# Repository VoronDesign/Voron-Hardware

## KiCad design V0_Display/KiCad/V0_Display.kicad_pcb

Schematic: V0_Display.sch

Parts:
C1, C2: 4.7uF; C_0805_2012Metric; LCSC C1779
C3, C4: 0.1uF; C_0805_2012Metric; LCSC C49678
D1: WS2812B; LED_WS2812B_PLCC4_5.0x5.0mm_P3.2mm
GPIO1: Conn_01x03; PinHeader_1x03_P2.54mm_Vertical
H1, H2, H3, H4: MountingHole; MountingHole_3.2mm_M3
J1: USB_B_Micro; MolexVertical&Horizontal_MicroB
J2: I2C Header 1; 1pt3in_OLED
J3: Conn_01x03; PinHeader_1x03_P2.54mm_Vertical
J4, J8: Conn_01x02; PinHeader_1x02_P2.54mm_Vertical
J5: SWD Header; PinHeader_2x05_P1.27mm_Vertical_SMD
J7: USB_Header; PinHeader_1x04_P2.54mm_Vertical
JP1: Pin2; SolderJumper-3_P1.3mm_Bridged12_Pad1.0x1.5mm
JP2: Pin1; SolderJumper-3_P1.3mm_Bridged12_Pad1.0x1.5mm
R1, R2, R3: 10K; R_0805_2012Metric; LCSC C17414
SW5, SW6: SW_SPST; SW_PUSH_6mm
SW7: Rotary_Encoder_Switch; EN11_Encoder
U1: AP2127K-3.3; SOT-23-5; LCSC C156285
U2: STM32F042F6Px; TSSOP-20_4.4x6.5mm_P0.65mm; LCSC C81000
U3: 74LVC1G17; SOT-753; LCSC C6076

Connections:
+3V3: C2.1, C3.2, C4.1, J4.1, J5.1, JP1.1, JP2.3, R1.1, R3.1, U1.5 (VOUT), U2.5, U2.16
BOOT0: J4.2, R2.1, U2.1
D+: J1.3, J7.3, U2.18
D-: J1.2, J7.2, U2.17
Encoder_A: SW7.A, U2.9
Encoder_B: SW7.B, U2.10
Encoder_Switch: SW7.S1, U2.7
GND: C1.2, C2.2, C3.1, C4.2, D1.3, J1.4, J1.5, J1.6, J5.3, J5.5, J7.4, J8.2, JP1.3, JP2.1, R2.2, SW5.2 (B), SW6.1, SW7.C, SW7.S2, U1.2 (GND), U2.15, U3.3
GPIO1: GPIO1.1, U2.12
GPIO2: GPIO1.2, U2.13
GPIO3: GPIO1.3, U2.14
Kill_Switch: SW6.2, U2.11
NeoPixel: U2.6, U3.2
unnamed: D1.2, J8.1
unnamed: D1.4, U3.4
Pin1: J2.1, JP2.2
Pin2: J2.2, JP1.2
SCL: J2.3, U2.3
SDA: J2.4, U2.2
SWDCLK: J3.2, J5.4, R3.2, U2.20
SWDIO: J3.1, J5.2, U2.19
VBUS: C1.1, D1.1, J1.1, J7.1, U1.1 (VIN), U1.3 (EN), U3.5
~Reset: J3.3, J5.10, R1.2, SW5.1 (A), U2.4

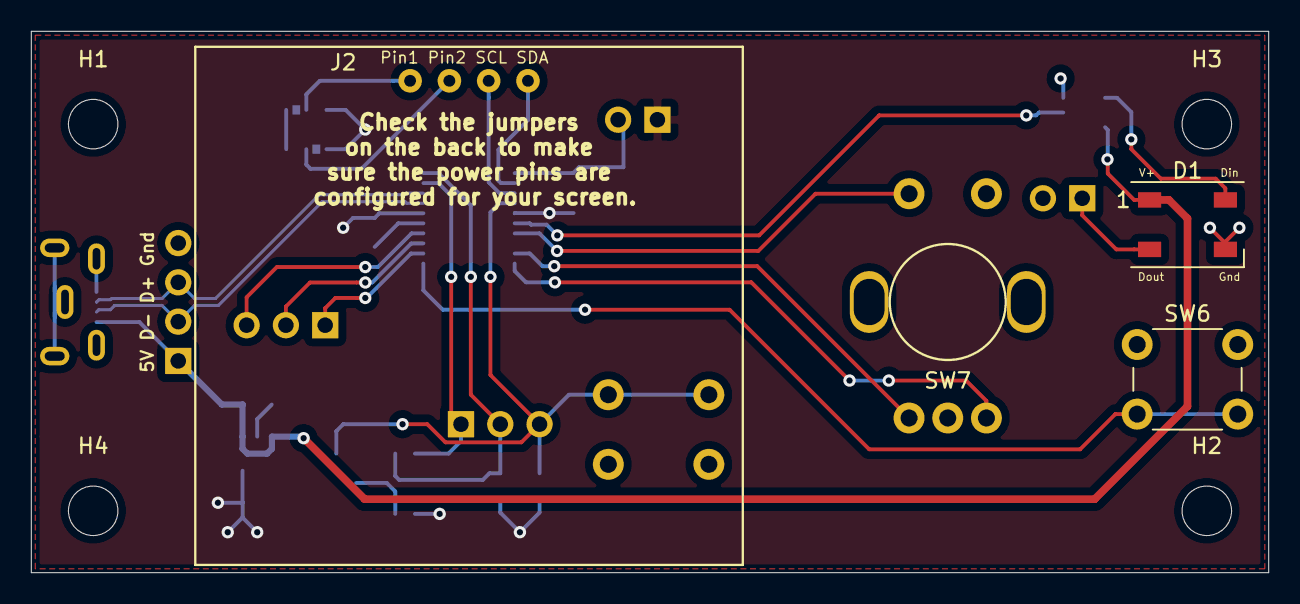
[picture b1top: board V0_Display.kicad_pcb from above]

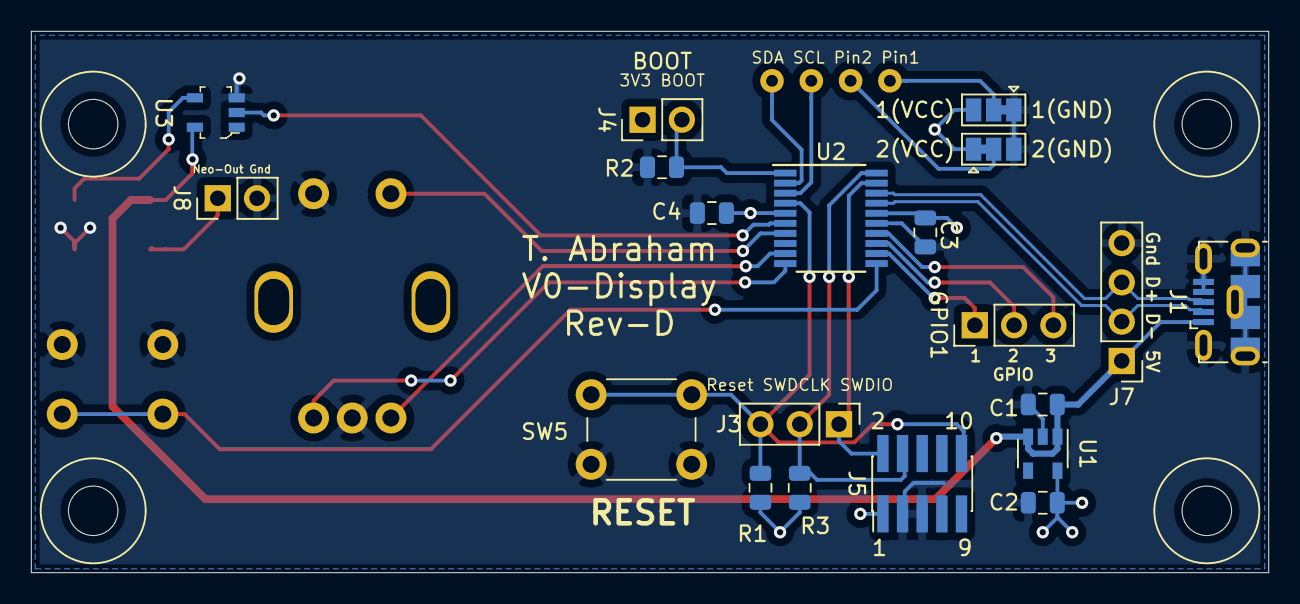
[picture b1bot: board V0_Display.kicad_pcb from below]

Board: 2 copper layers, 80.0 x 35.0 mm, 28 parts (20 on the bottom side), 23 nets.

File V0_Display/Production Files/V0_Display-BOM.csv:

"Comment","Designator","Footprint","LCSC","Notes",
"4.7uF","C1,C2","V0-Display:C_0805_2012Metric","C1779","4.7uF 0805 capacitor",
"0.1uF","C3,C4","V0-Display:C_0805_2012Metric","C49678","0.1uF 0805 capacitor",
"WS2812B","D1","V0-Display:LED_WS2812B_PLCC4_5.0x5.0mm_P3.2mm","","Neopixel LED",
"MountingHole","H1,H2,H3,H4","V0-Display:MountingHole_3.2mm_M3","","Unpopulated",
"USB_B_Micro","J1","V0-Display:MolexVertical&Horizontal_MicroB","","Molex 1050170001",
"I2C Header 1","J2","V0-Display:1pt3in_OLED","","OLED goes here",
"Conn_01x03","J3,GPIO1","V0-Display:PinHeader_1x03_P2.54mm_Vertical","","GPIO pins",
"Conn_01x02","J4,J8","V0-Display:PinHeader_1x02_P2.54mm_Vertical","","Boot Jumper (J4) and Neopixel Data Out (J8)",
"SWD Header","J5","V0-Display:PinHeader_2x05_P1.27mm_Vertical_SMD","","Not necessary for normal operation",
"USB_Header","J7","V0-Display:PinHeader_1x04_P2.54mm_Vertical","","Use instead of USB connector if desired (JST-XH or compatable)",
"Pin2","JP1","V0-Display:SolderJumper-3_P1.3mm_Bridged12_Pad1.0x1.5mm","","SMD Jumper for I2C power/ground pins",
"Pin1","JP2","V0-Display:SolderJumper-3_P1.3mm_Bridged12_Pad1.0x1.5mm","","SMD Jumper for I2C power/ground pins",
"10K","R2,R1,R3","V0-Display:R_0805_2012Metric","C17414","10K 0805 resistor",
"SW_SPST","SW1,SW2,SW3,SW4,SW5,SW6","V0-Display:SW_PUSH_6mm","","4.3mm tall required",
"Rotary_Encoder_Switch","SW7","V0-Display:EN11_Encoder","","EN11-HSB1AF15 or equivalent",
"AP2127K-3.3","U1","V0-Display:SOT-23-5","C156285","Voltage Regulator",
"STM32F042F6Px","U2","V0-Display:TSSOP-20_4.4x6.5mm_P0.65mm","C81000"," MCU ",
"74LVC1G17","U3","V0-Display:SOT-753","C6076"," Buffer",

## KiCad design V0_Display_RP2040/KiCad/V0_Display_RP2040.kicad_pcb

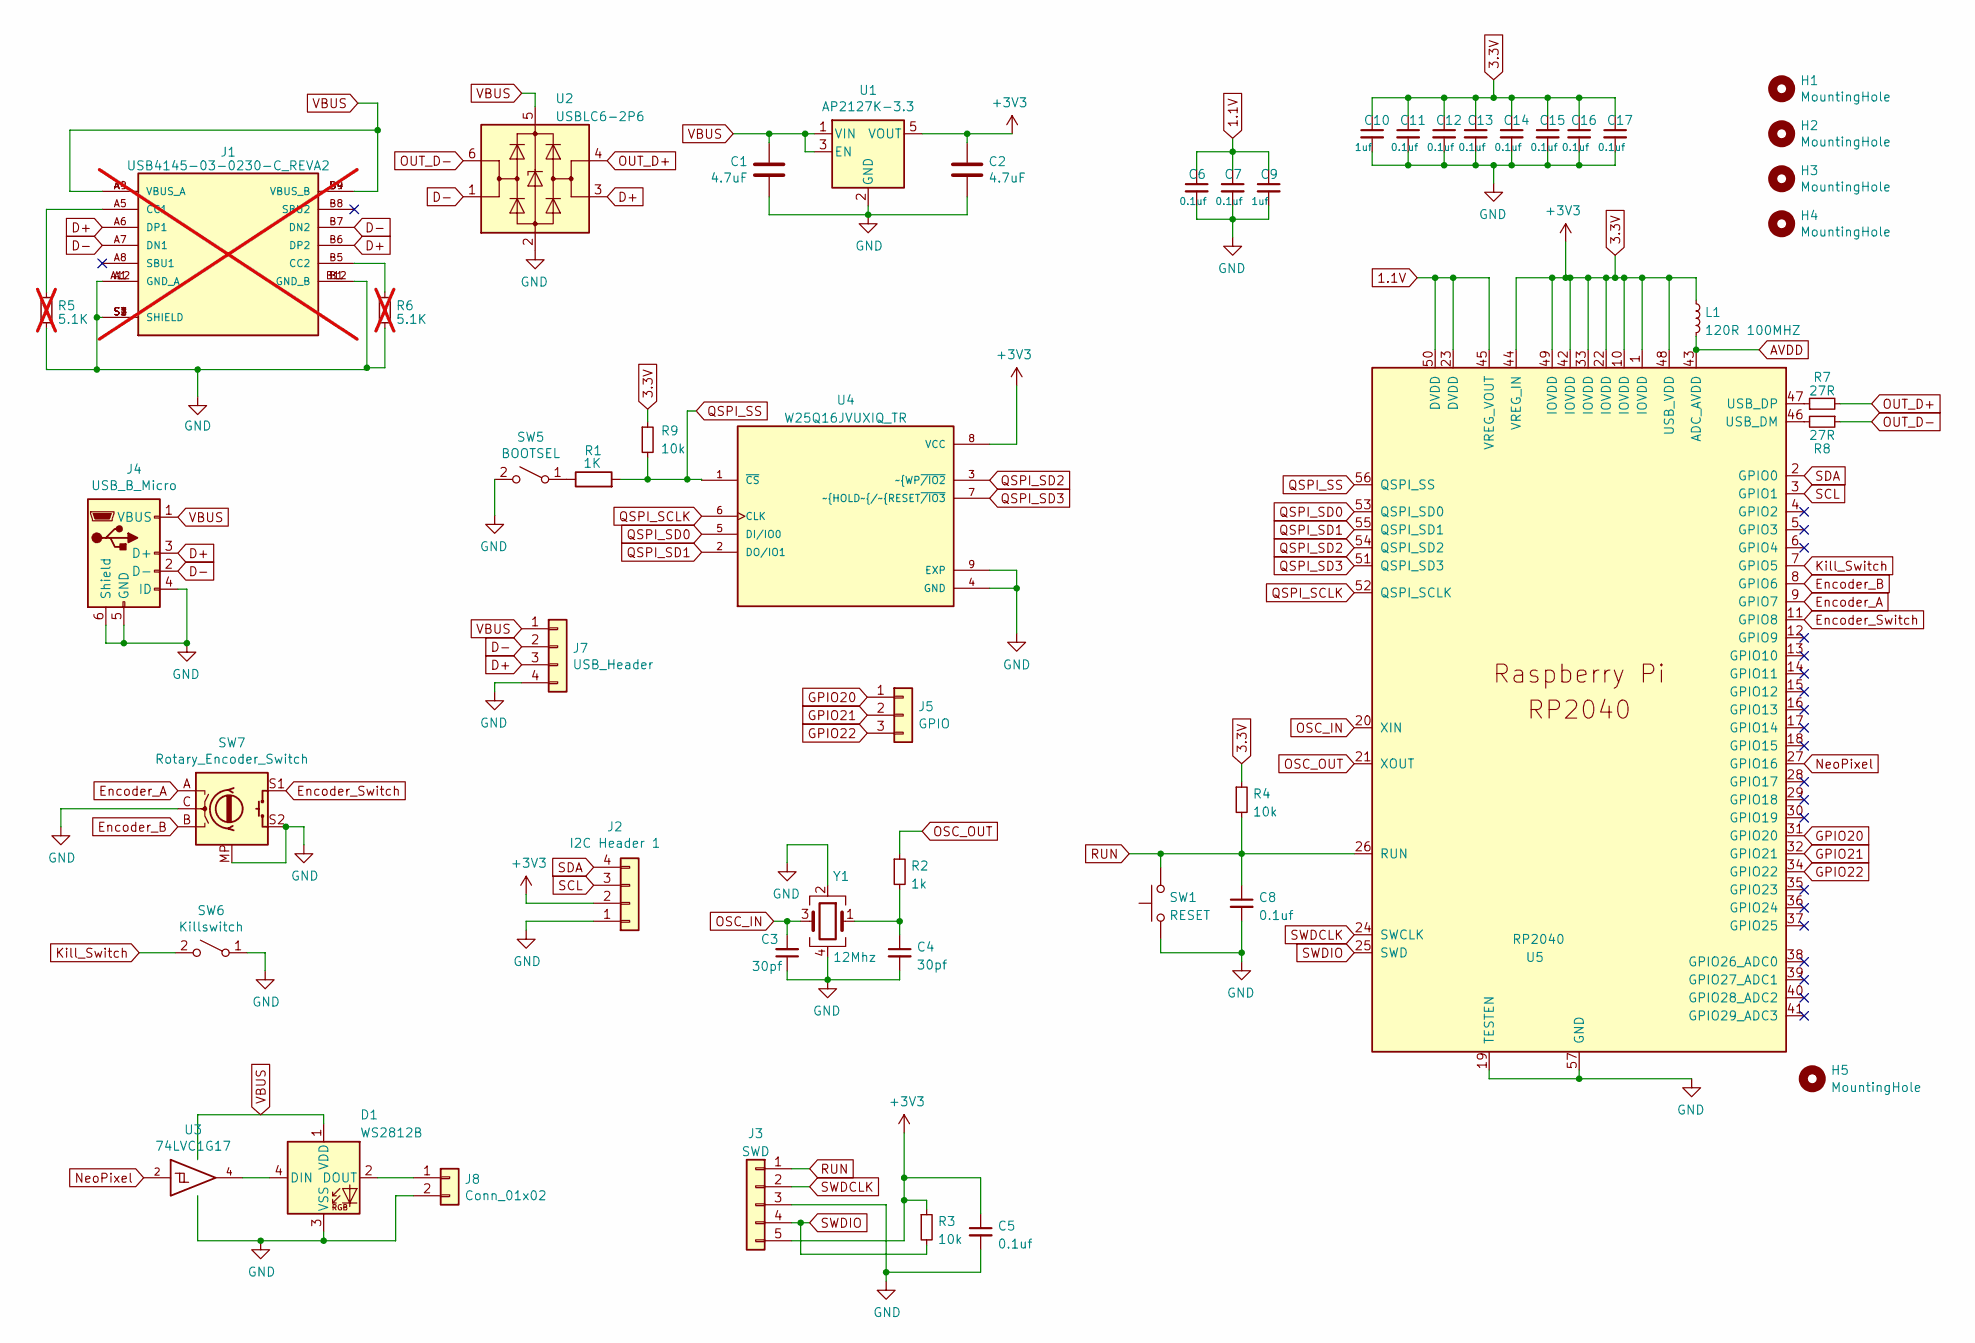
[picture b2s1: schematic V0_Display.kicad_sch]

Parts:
C1, C2: 4.7uF; C_0603_1608Metric; LCSC C19666
C3, C4: 30pf; C_0402_1005Metric; LCSC C526980
C5, C6, C7, C8, C11, C12, C13, C14, C15, C16, C17: 0.1uf; C_0402_1005Metric; LCSC C1525
C9, C10: 1uf; C_0402_1005Metric; LCSC C52923
D1: WS2812B; LED_WS2812B_PLCC4_5.0x5.0mm_P3.2mm; LCSC C2761795
H1, H2, H3, H4: MountingHole; MountingHole_3.2mm_M3
H5: MountingHole; VoronLogo_6pt5mm_silkScreen
J1: USB4145-03-0230-C_REVA2; GCT_USB4145-03-0230-C_REVA2; MPN USB4145-03-0230-C; LCSC C5291559; not fitted
J2: I2C Header 1; 1pt3in_OLED
J3: SWD; PinHeader_1x05_P2.54mm_Vertical
J4: USB_B_Micro; MolexVertical&Horizontal_MicroB; LCSC C136000
J5: GPIO; PinHeader_1x03_P2.54mm_Vertical
J7: USB_Header; PinHeader_1x04_P2.54mm_Vertical
J8: Conn_01x02; PinHeader_1x02_P2.54mm_Vertical
L1: 120R 100MHZ; L_0402_1005Metric; LCSC C107331
R1: 1K; R_0603_1608Metric; LCSC C21190
R2: 1k; R_0603_1608Metric; LCSC C21190
R3, R4, R9: 10k; R_0603_1608Metric; LCSC C25804
R5, R6: 5.1K; R_0603_1608Metric; LCSC C23186; not fitted
R7, R8: 27R; R_0402_1005Metric; LCSC C137890
SW1: RESET; SW_Push_1P1T_NO_4.5x4.5mm; LCSC C843607
SW5: BOOTSEL; SW_Push_1P1T_NO_4.5x4.5mm; LCSC C843607
SW6: Killswitch; SW_Push_1P1T_NO_4.5x4.5mm; LCSC C843607
SW7: Rotary_Encoder_Switch; EN11_Encoder; MPN EN11-HSB1AF15
U1: AP2127K-3.3; SOT-23-5; LCSC C156285
U2: USBLC6-2P6; SOT-666; LCSC C2827693
U3: 74LVC1G17; SOT-753; LCSC C6076
U4: W25Q16JVUXIQ_TR; IC_W25Q16JVUXIQ_TR; LCSC C2843335
U5: RP2040; RP2040-QFN-56; LCSC C2040
Y1: 12Mhz; Crystal_SMD_3225-4Pin_3.2x2.5mm; LCSC C133334

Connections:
1.1V: C6.1, C7.1, C9.1, U5.23 (DVDD), U5.45 (VREG_VOUT), U5.50 (DVDD)
3.3V: C2.1, C5.1, C10.1, C11.1, C12.1, C13.1, C14.1, C15.1, C16.1, C17.1, J2.2, J3.5, L1.1, R3.1, R4.1, R9.1, U1.5 (VOUT), U4.8 (VCC), U5.1 (IOVDD), U5.10 (IOVDD), U5.22 (IOVDD), U5.33 (IOVDD), U5.42 (IOVDD), U5.44 (VREG_IN), U5.48 (USB_VDD), U5.49 (IOVDD)
AVDD: L1.2, U5.43 (ADC_AVDD)
D+: J1.A6 (DP1), J1.B6 (DP2), J4.3 (D+), J7.3, U2.3 (I/O2)
D-: J1.A7 (DN1), J1.B7 (DN2), J4.2 (D-), J7.2, U2.1 (I/O1)
Encoder_A: SW7.A, U5.9 (GPIO7)
Encoder_B: SW7.B, U5.8 (GPIO6)
Encoder_Switch: SW7.S1, U5.11 (GPIO8)
GND: C1.2, C2.2, C3.1, C4.2, C5.2, C6.2, C7.2, C8.2, C9.2, C10.2, C11.2, C12.2, C13.2, C14.2, C15.2, C16.2, C17.2, D1.3 (VSS), J1.A1 (GND_A), J1.A12 (GND_A), J1.B1 (GND_B), J1.B12 (GND_B), J1.S1 (SHIELD), J1.S2 (SHIELD), J1.S3 (SHIELD), J1.S4 (SHIELD), J2.1, J3.3, J4.4 (ID), J4.5 (GND), J4.6 (Shield), J7.4, J8.2, R5.1, R6.2, SW1.1, SW5.2 (B), SW6.1 (A), SW7.C, SW7.MP, SW7.S2, U1.2 (GND), U2.2 (GND), U3.3 (GND), U4.4 (GND), U4.9 (EXP), U5.19 (TESTEN), U5.57 (GND), Y1.2, Y1.4
GPIO20: J5.1, U5.31 (GPIO20)
GPIO21: J5.2, U5.32 (GPIO21)
GPIO22: J5.3, U5.34 (GPIO22)
Kill_Switch: SW6.2 (B), U5.7 (GPIO5)
NeoPixel: U3.2, U5.27 (GPIO16)
unnamed: C4.1, R2.2, Y1.1
unnamed: D1.4 (DIN), U3.4
unnamed: D1.2 (DOUT), J8.1
unnamed: J1.A5 (CC1), R5.2
unnamed: J1.B5 (CC2), R6.1
unnamed: R1.1, SW5.1 (A)
unnamed: R8.2, U5.46 (USB_DM)
unnamed: R7.1, U5.47 (USB_DP)
OSC_IN: C3.2, U5.20 (XIN), Y1.3
OSC_OUT: R2.1, U5.21 (XOUT)
OUT_D+: R7.2, U2.4 (I/O2)
OUT_D-: R8.1, U2.6 (I/O1)
QSPI_SCLK: U4.6 (CLK), U5.52 (QSPI_SCLK)
QSPI_SD0: U4.5 (DI/IO0), U5.53 (QSPI_SD0)
QSPI_SD1: U4.2 (DO/IO1), U5.55 (QSPI_SD1)
QSPI_SD2: U4.3 (~WP~{/IO2), U5.54 (QSPI_SD2)
QSPI_SD3: U4.7 (~HOLD~{/~{RESET~{/IO3), U5.51 (QSPI_SD3)
QSPI_SS: R1.2, R9.2, U4.1 (~CS), U5.56 (QSPI_SS)
RUN: C8.1, J3.1, R4.2, SW1.2, U5.26 (RUN)
SCL: J2.3, U5.3 (GPIO1)
SDA: J2.4, U5.2 (GPIO0)
SWDCLK: J3.2, U5.24 (SWCLK)
SWDIO: J3.4, R3.2, U5.25 (SWD)
VBUS: C1.1, D1.1 (VDD), J1.A4 (VBUS_A), J1.A9 (VBUS_A), J1.B4 (VBUS_B), J1.B9 (VBUS_B), J4.1 (VBUS), J7.1, U1.1 (VIN), U1.3 (EN), U2.5 (VBUS), U3.5 (VCC)

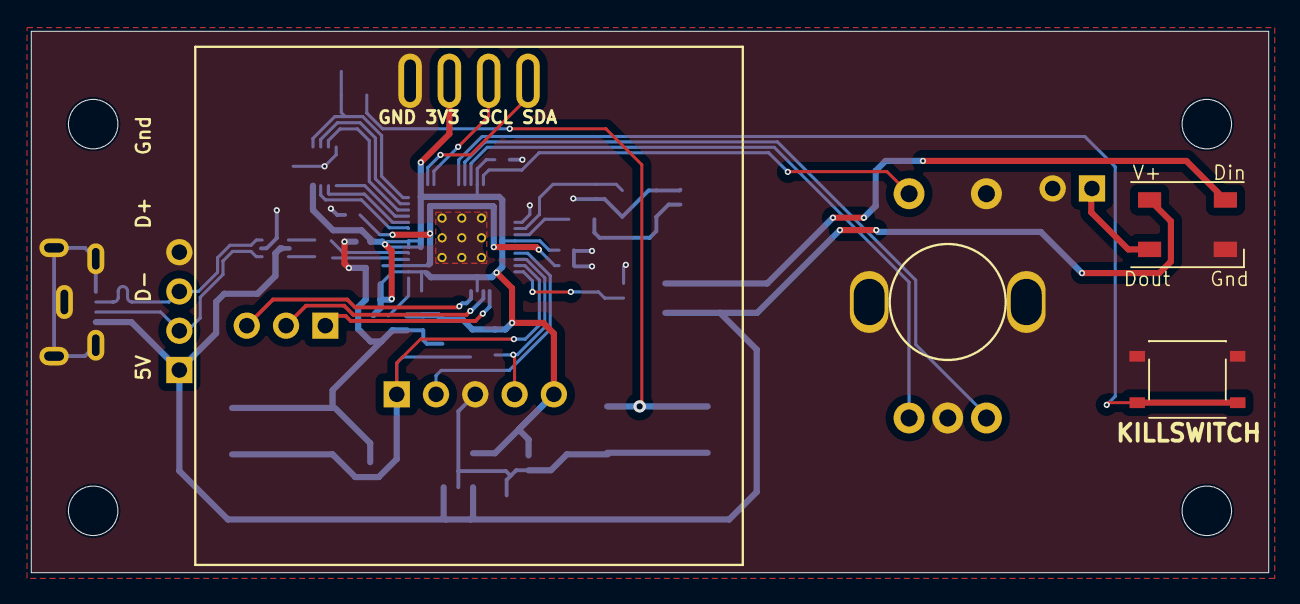
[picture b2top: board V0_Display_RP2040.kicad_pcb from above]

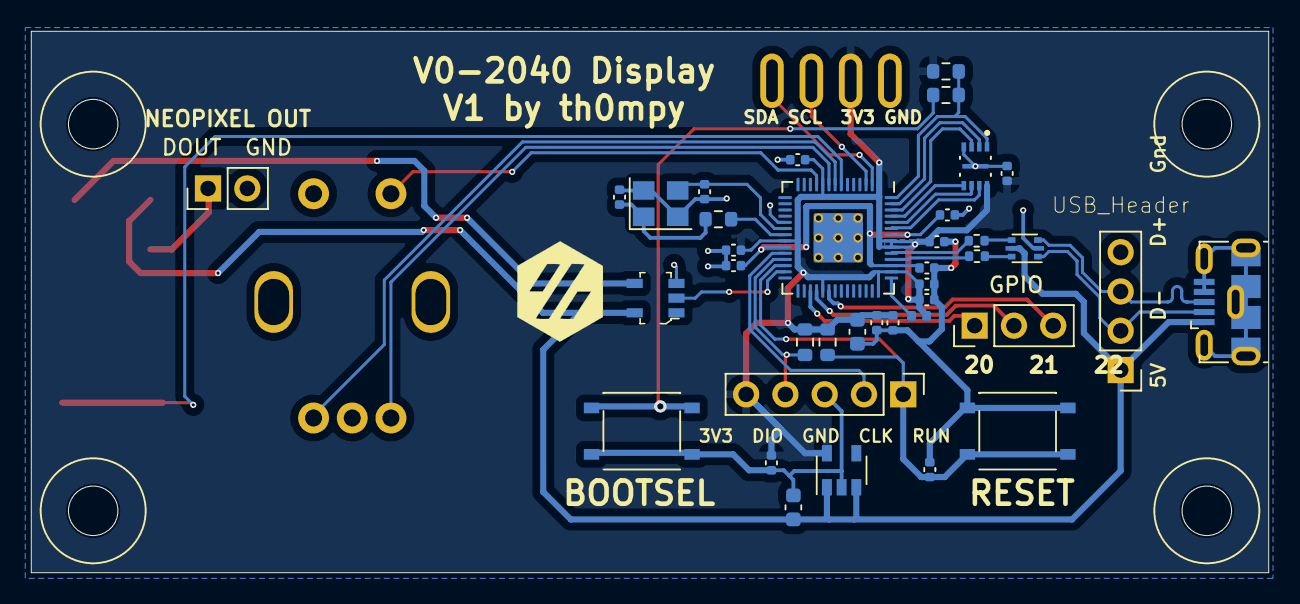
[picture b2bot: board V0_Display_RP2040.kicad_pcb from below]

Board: 2 copper layers, 80.0 x 35.0 mm, 47 parts (39 on the bottom side), 36 nets.

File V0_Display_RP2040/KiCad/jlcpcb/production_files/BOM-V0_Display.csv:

Comment,Designator,Footprint,LCSC
"4.7uF","C1,C2","Voron0 2040 display:C_0603_1608Metric","C326580"
"30pf","C3,C4","Voron0 2040 display:C_0402_1005Metric","C526980"
"0.1uf","C5,C6,C7,C8,C11,C12,C13,C14,C15,C16,C17","Voron0 2040 display:C_0402_1005Metric","C129131"
"1uf","C9,C10","Voron0 2040 display:C_0402_1005Metric","C106254"
"WS2812B","D1","Voron0 2040 display:LED_WS2812B_PLCC4_5.0x5.0mm_P3.2mm","C114586"
"USB4145-03-0230-C_REVA2","J1","USB4145-03-0230-C_REVA2:GCT_USB4145-03-0230-C_REVA2","C5291559"
"120R 100MHZ","L1","Voron0 2040 display:L_0402_1005Metric","C107331"
"1K","R1","Voron0 2040 display:R_0603_1608Metric","C4295595"
"1k","R2","Voron0 2040 display:R_0402_1005Metric","C852624"
"10k","R3,R4","Voron0 2040 display:R_0603_1608Metric","C2139679"
"5.1K","R5,R6","Voron0 2040 display:R_0402_1005Metric","C105873"
"27R","R7,R8","Voron0 2040 display:R_0402_1005Metric","C137890"
"RESET","SW1","Library:SW_Push_1P1T_NO_4.5x4.5mm","C843607"
"BOOTSEL","SW5","Library:SW_Push_1P1T_NO_4.5x4.5mm","C843607"
"Killswitch","SW6","Library:SW_Push_1P1T_NO_4.5x4.5mm","C843607"
"AP2127K-3.3","U1","Voron0 2040 display:SOT-23-5","C156285"
"USBLC6-2P6","U2","Voron0 2040 display:SOT-666","C2827693"
"74LVC1G17","U3","Voron0 2040 display:SOT-753","C6076"
"W25Q16JVUXIQ_TR","U4","Voron0 2040 display:IC_W25Q16JVUXIQ_TR","C2843335"
"RP2040","U5","Voron0 2040 display:RP2040-QFN-56","C2040"
"12Mhz","Y1","Voron0 2040 display:Crystal_SMD_3225-4Pin_3.2x2.5mm","C133334"

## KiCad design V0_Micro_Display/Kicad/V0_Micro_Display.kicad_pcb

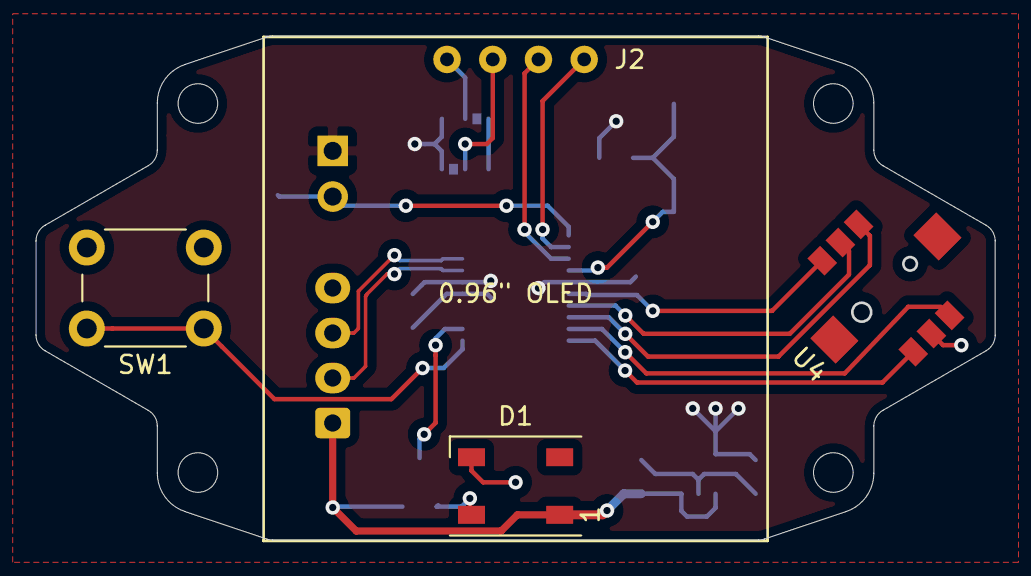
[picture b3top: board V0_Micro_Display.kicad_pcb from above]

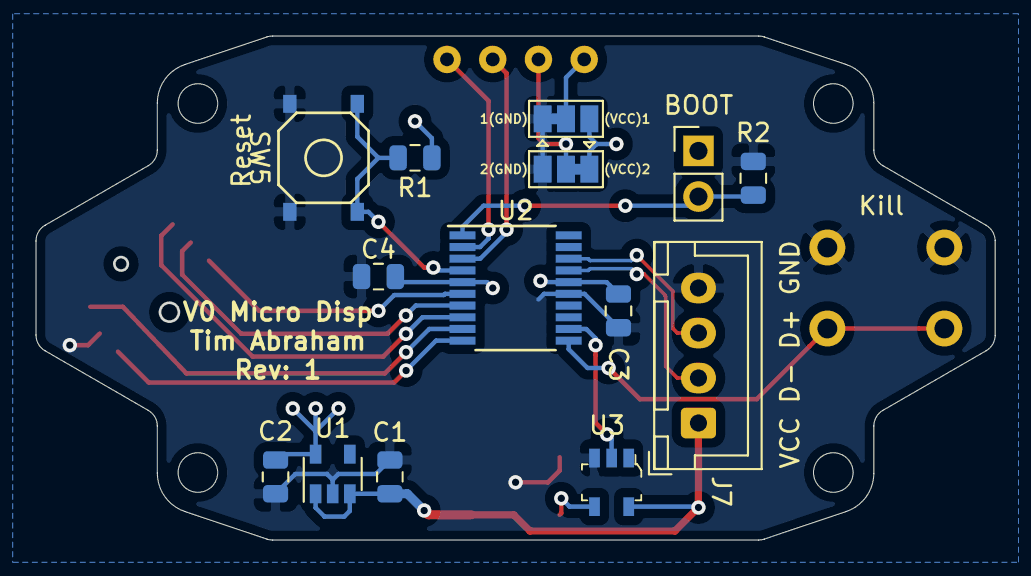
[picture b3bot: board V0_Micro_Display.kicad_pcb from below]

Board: 2 copper layers, 53.3 x 28.0 mm, 18 parts (14 on the bottom side), 19 nets.

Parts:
C1, C2: 4.7uF; C_0805_2012Metric
C3, C4: 0.1uF; C_0805_2012Metric
D1: WS2812B; LED_WS2812B_PLCC4_5.0x5.0mm_P3.2mm
J2: I2C Header 1; 0pt96in_OLED
J4: Conn_01x02; PinHeader_1x02_P2.54mm_Vertical
J7: USB_Header; JST_XH_B4B-XH-A_1x04_P2.50mm_Vertical
JP1: Pin2; SolderJumper-3_P1.3mm_Bridged12_Pad1.0x1.5mm
JP2: Pin1; SolderJumper-3_P1.3mm_Bridged12_Pad1.0x1.5mm
R1, R2: 10K; R_0805_2012Metric
SW1: SW_SPST; SW_PUSH_6mm
SW5: SW_SPST; TS-1187A-B-A-B
U1: AP2127K-3.3; SOT-23-5
U2: STM32F042F6Px; TSSOP-20_4.4x6.5mm_P0.65mm
U3: 74LVC1G17; SOT-753
U4: Alps_4-Way_Joystick

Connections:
+3V3: C2.1, C3.2, C4.1, J4.1, JP1.1, JP2.3, R1.1, U1.5, U2.5, U2.16
BOOT0: J4.2, R2.1, U2.1
Button_Down: U2.10, U4.6
Button_Left: U2.6, U4.3
Button_Right: U2.9, U4.4
Button_Up: U2.8, U4.1
Center: U2.7, U4.2
D+: J7.3, U2.18
D-: J7.2, U2.17
GND: C1.2, C2.2, C3.1, C4.2, D1.3, J7.4, JP1.3, JP2.1, R2.2, SW1.2, SW5.2, U1.2, U2.15, U3.3, U4.5
Kill_Switch: SW1.1, U2.11
NeoPixel: U2.12, U3.2
unnamed: D1.4, U3.4
Pin1: J2.1, JP2.2
Pin2: J2.2, JP1.2
SCL: J2.3, U2.3
SDA: J2.4, U2.2
VBUS: C1.1, D1.1, J7.1, U1.1, U1.3, U3.5
~Reset: R1.2, SW5.1, U2.4

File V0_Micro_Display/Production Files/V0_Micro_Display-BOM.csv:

"Comment","Designator","Footprint","LCSC"
"4.7uF","C1,C2","V0-Micro-Display:C_0805_2012Metric","C1779"
"0.1uF","C3,C4","V0-Micro-Display:C_0805_2012Metric","C49678"
"WS2812B","D1","V0-Micro-Display:LED_WS2812B_PLCC4_5.0x5.0mm_P3.2mm","C114586"
"I2C Header 1","J2","V0-Micro-Display:0pt96in_OLED","-"
"Conn_01x02","J4","V0-Micro-Display:PinHeader_1x02_P2.54mm_Vertical","C160332"
"USB_Header","J7","Connector_JST:JST_XH_B4B-XH-A_1x04_P2.50mm_Vertical","C144395"
"Pin2","JP1","V0-Micro-Display:SolderJumper-3_P1.3mm_Bridged12_Pad1.0x1.5mm","-"
"Pin1","JP2","V0-Micro-Display:SolderJumper-3_P1.3mm_Bridged12_Pad1.0x1.5mm","-"
"10K","R2,R1","V0-Micro-Display:R_0805_2012Metric","C17414"
"SW_SPST","SW1","V0-Micro-Display:SW_PUSH_6mm","C620201"
"SW_SPST","SW5","V0-Micro-Display:TS-1187A-B-A-B","C318884"
"AP2127K-3.3","U1","V0-Micro-Display:SOT-23-5","C156285"
"STM32F042F6Px","U2","V0-Micro-Display:TSSOP-20_4.4x6.5mm_P0.65mm","C81000"
"74LVC1G17","U3","V0-Micro-Display:SOT-753","C6076"
"Alps_4-Way_Joystick","U4","V0-Micro-Display:Alps_4-Way_Joystick","C202423"
